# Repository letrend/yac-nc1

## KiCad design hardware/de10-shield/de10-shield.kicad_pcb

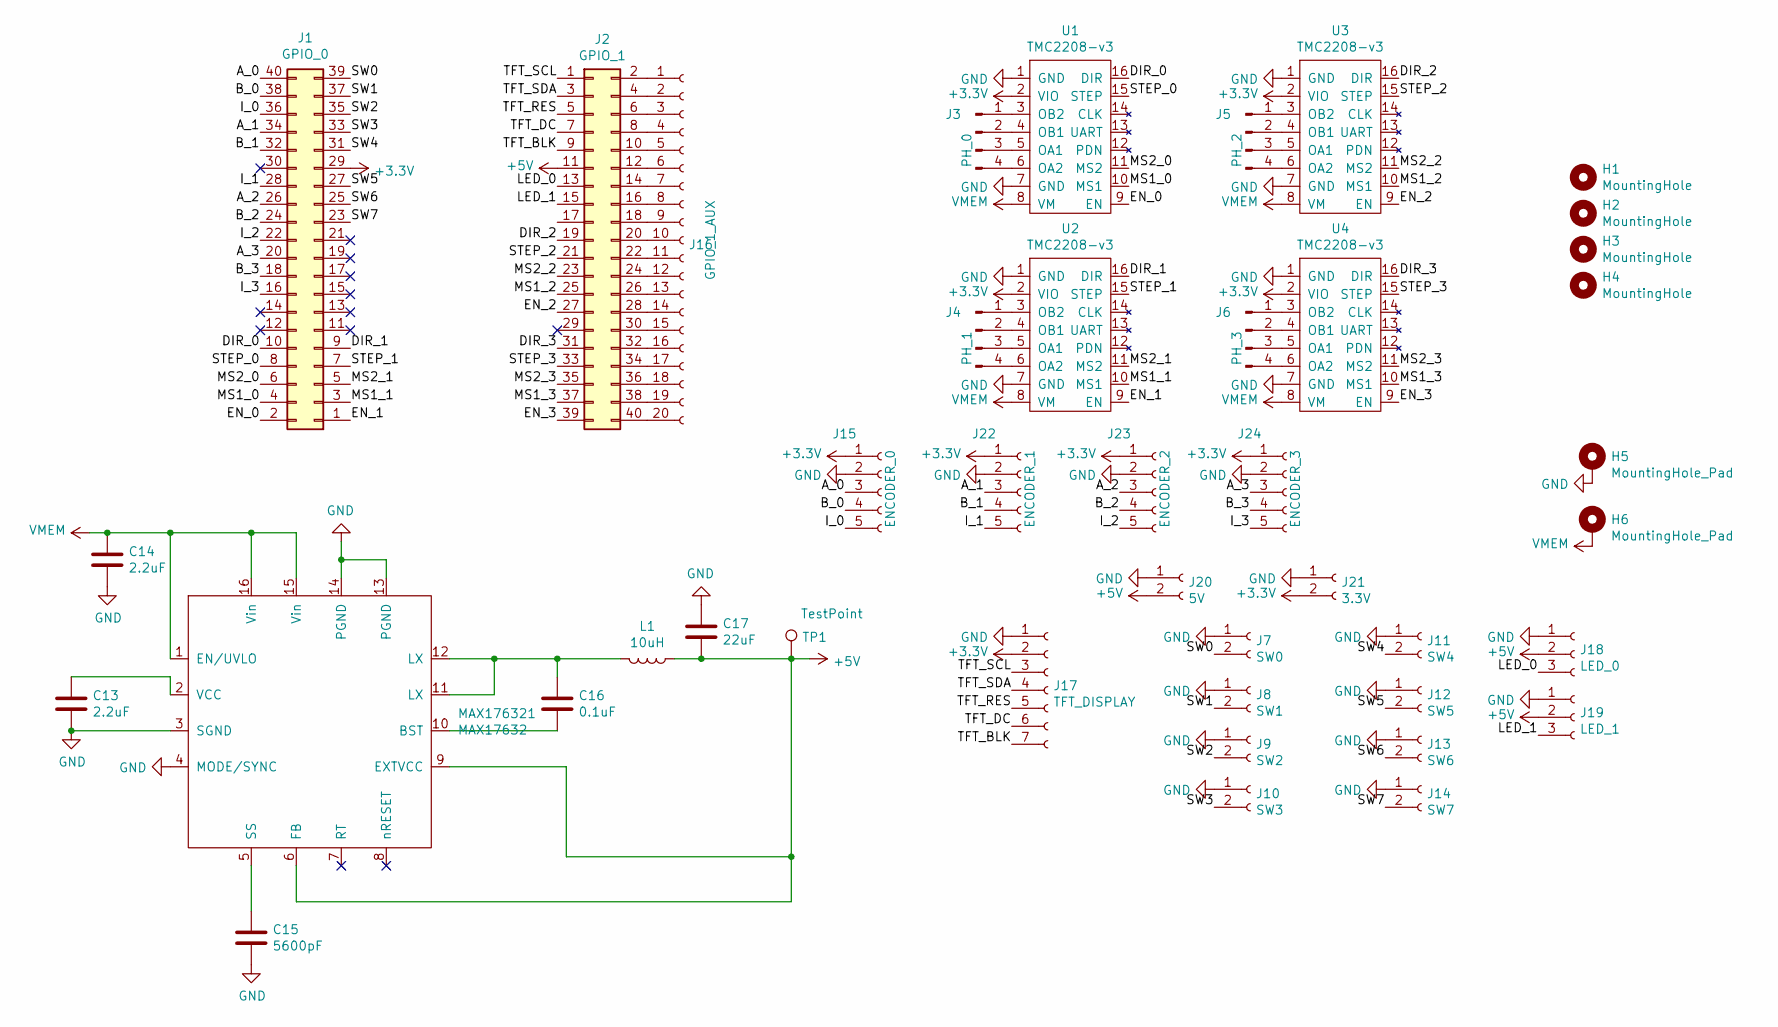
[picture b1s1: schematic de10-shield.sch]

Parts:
C13, C14: 2.2uF; C_0603_1608Metric
C15: 5600pF; C_0402_1005Metric
C16: 0.1uF; C_0402_1005Metric
C17: 22uF; C_0805_2012Metric
H1, H2, H3, H4: MountingHole; MountingHole_3.2mm_M3
H5, H6: MountingHole_Pad; MountingHole_3.2mm_M3_DIN965_Pad
J1: GPIO_0; PinSocket_2x20_P2.54mm_Vertical
J2: GPIO_1; PinSocket_2x20_P2.54mm_Vertical
J3: PH_0; PinHeader_1x04_P2.54mm_Vertical
J4: PH_1; PinHeader_1x04_P2.54mm_Vertical
J5: PH_2; PinHeader_1x04_P2.54mm_Vertical
J6: PH_3; PinHeader_1x04_P2.54mm_Vertical
J7: SW0; PinHeader_1x02_P2.54mm_Vertical
J8: SW1; PinHeader_1x02_P2.54mm_Vertical
J9: SW2; PinHeader_1x02_P2.54mm_Vertical
J10: SW3; PinHeader_1x02_P2.54mm_Vertical
J11: SW4; PinHeader_1x02_P2.54mm_Vertical
J12: SW5; PinHeader_1x02_P2.54mm_Vertical
J13: SW6; PinHeader_1x02_P2.54mm_Vertical
J14: SW7; PinHeader_1x02_P2.54mm_Vertical
J15: ENCODER_0; PinSocket_1x05_P2.54mm_Vertical
J16: GPIO_1_AUX; PinSocket_1x20_P2.54mm_Vertical
J17: TFT_DISPLAY; PinHeader_1x07_P2.54mm_Vertical
J18: LED_0; PinHeader_1x03_P2.54mm_Vertical
J19: LED_1; PinHeader_1x03_P2.54mm_Vertical
J20: 5V; PinHeader_1x02_P2.54mm_Vertical
J21: 3.3V; PinHeader_1x02_P2.54mm_Vertical
J22: ENCODER_1; PinSocket_1x05_P2.54mm_Vertical
J23: ENCODER_2; PinSocket_1x05_P2.54mm_Vertical
J24: ENCODER_3; PinSocket_1x05_P2.54mm_Vertical
L1: 10uH; XAL5050-103MEC
MAX176321: MAX17632; QFN-16-1EP_3x3mm_Pitch0.5mm
TP1: TestPoint; TestPoint_Pad_D1.0mm
U1, U2, U3, U4: TMC2208-v3; TMC2208-v3.0

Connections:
+3V3: J1.29, J15.1, J17.2, J21.2, J22.1, J23.1, J24.1, U1.2 (VIO), U2.2 (VIO), U3.2 (VIO), U4.2 (VIO)
+5V: C17.2, J2.11, J18.2, J19.2, J20.2, L1.1, MAX176321.6 (FB), MAX176321.9 (EXTVCC), TP1.1
/A_0: J1.40, J15.3
/A_1: J1.34, J22.3
/A_2: J1.26, J23.3
/A_3: J1.20, J24.3
/B_0: J1.38, J15.4
/B_1: J1.32, J22.4
/B_2: J1.24, J23.4
/B_3: J1.18, J24.4
/DIR_0: J1.10, U1.16 (DIR)
/DIR_1: J1.9, U2.16 (DIR)
/DIR_2: J2.19, U3.16 (DIR)
/DIR_3: J2.31, U4.16 (DIR)
/EN_0: J1.2, U1.9 (EN)
/EN_1: J1.1, U2.9 (EN)
/EN_2: J2.27, U3.9 (EN)
/EN_3: J2.39, U4.9 (EN)
/I_0: J1.36, J15.5
/I_1: J1.28, J22.5
/I_2: J1.22, J23.5
/I_3: J1.16, J24.5
/LED_0: J2.13, J18.3
/LED_1: J2.15, J19.3
/MS1_0: J1.4, U1.10 (MS1)
/MS1_1: J1.3, U2.10 (MS1)
/MS1_2: J2.25, U3.10 (MS1)
/MS1_3: J2.37, U4.10 (MS1)
/MS2_0: J1.6, U1.11 (MS2)
/MS2_1: J1.5, U2.11 (MS2)
/MS2_2: J2.23, U3.11 (MS2)
/MS2_3: J2.35, U4.11 (MS2)
/STEP_0: J1.8, U1.15 (STEP)
/STEP_1: J1.7, U2.15 (STEP)
/STEP_2: J2.21, U3.15 (STEP)
/STEP_3: J2.33, U4.15 (STEP)
/SW0: J1.39, J7.2
/SW1: J1.37, J8.2
/SW2: J1.35, J9.2
/SW3: J1.33, J10.2
/SW4: J1.31, J11.2
/SW5: J1.27, J12.2
/SW6: J1.25, J13.2
/SW7: J1.23, J14.2
/TFT_BLK: J2.9, J17.7
/TFT_DC: J2.7, J17.6
/TFT_RES: J2.5, J17.5
/TFT_SCL: J2.1, J17.3
/TFT_SDA: J2.3, J17.4
GND: C13.2, C14.2, C15.2, C17.1, H5.1, J7.1, J8.1, J9.1, J10.1, J11.1, J12.1, J13.1, J14.1, J15.2, J17.1, J18.1, J19.1, J20.1, J21.1, J22.2, J23.2, J24.2, MAX176321.3 (SGND), MAX176321.4 (MODE/SYNC), MAX176321.13 (PGND), MAX176321.14 (PGND), U1.1 (GND), U1.7 (GND), U2.1 (GND), U2.7 (GND), U3.1 (GND), U3.7 (GND), U4.1 (GND), U4.7 (GND); also elsewhere on the board
unnamed: C13.1, MAX176321.2 (VCC)
unnamed: C15.1, MAX176321.5 (SS)
unnamed: C16.1, L1.2, MAX176321.11 (LX), MAX176321.12 (LX)
unnamed: C16.2, MAX176321.10 (BST)
unnamed: J3.1, U1.3 (OB2)
unnamed: J3.2, U1.4 (OB1)
unnamed: J3.3, U1.5 (OA1)
unnamed: J3.4, U1.6 (OA2)
unnamed: J4.1, U2.3 (OB2)
unnamed: J4.2, U2.4 (OB1)
unnamed: J4.3, U2.5 (OA1)
unnamed: J4.4, U2.6 (OA2)
unnamed: J5.1, U3.3 (OB2)
unnamed: J5.2, U3.4 (OB1)
unnamed: J5.3, U3.5 (OA1)
unnamed: J5.4, U3.6 (OA2)
unnamed: J6.1, U4.3 (OB2)
unnamed: J6.2, U4.4 (OB1)
unnamed: J6.3, U4.5 (OA1)
unnamed: J6.4, U4.6 (OA2)
unnamed: J2.2, J16.1
unnamed: J2.4, J16.2
unnamed: J2.6, J16.3
unnamed: J2.8, J16.4
unnamed: J2.10, J16.5
unnamed: J2.12, J16.6
unnamed: J2.14, J16.7
unnamed: J2.16, J16.8
unnamed: J2.18, J16.9
unnamed: J2.20, J16.10
unnamed: J2.22, J16.11
unnamed: J2.24, J16.12
unnamed: J2.26, J16.13
unnamed: J2.28, J16.14
unnamed: J2.30, J16.15
unnamed: J2.32, J16.16
unnamed: J2.34, J16.17
unnamed: J2.36, J16.18
unnamed: J2.38, J16.19
unnamed: J2.40, J16.20
VMEM: C14.1, H6.1, MAX176321.1 (EN/UVLO), MAX176321.15 (Vin), MAX176321.16 (Vin), U1.8 (VM), U2.8 (VM), U3.8 (VM), U4.8 (VM)

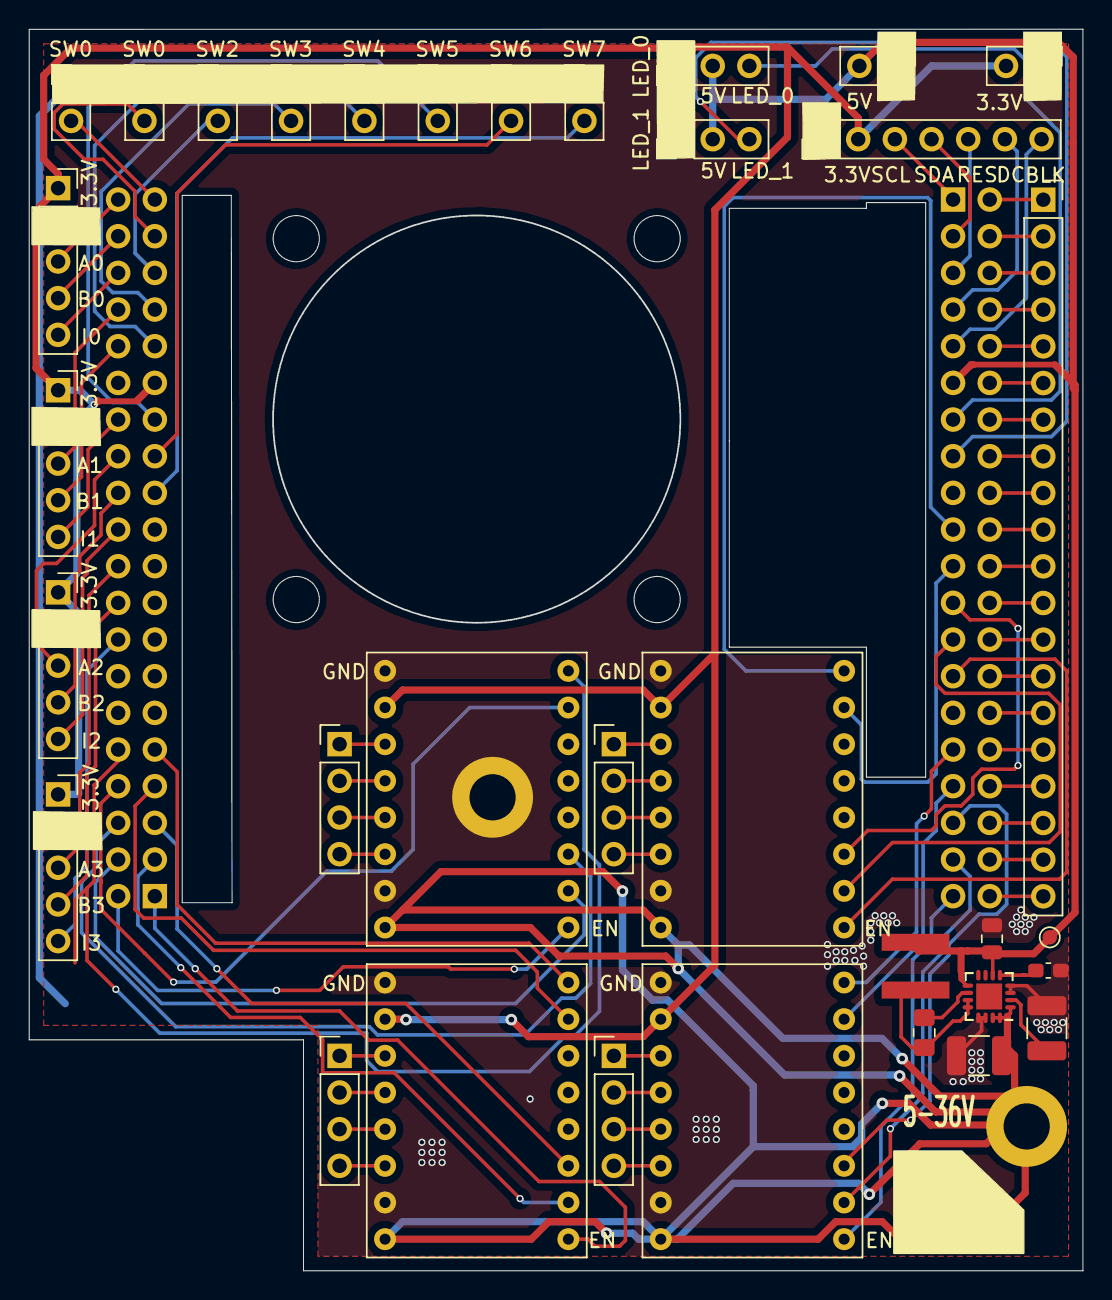
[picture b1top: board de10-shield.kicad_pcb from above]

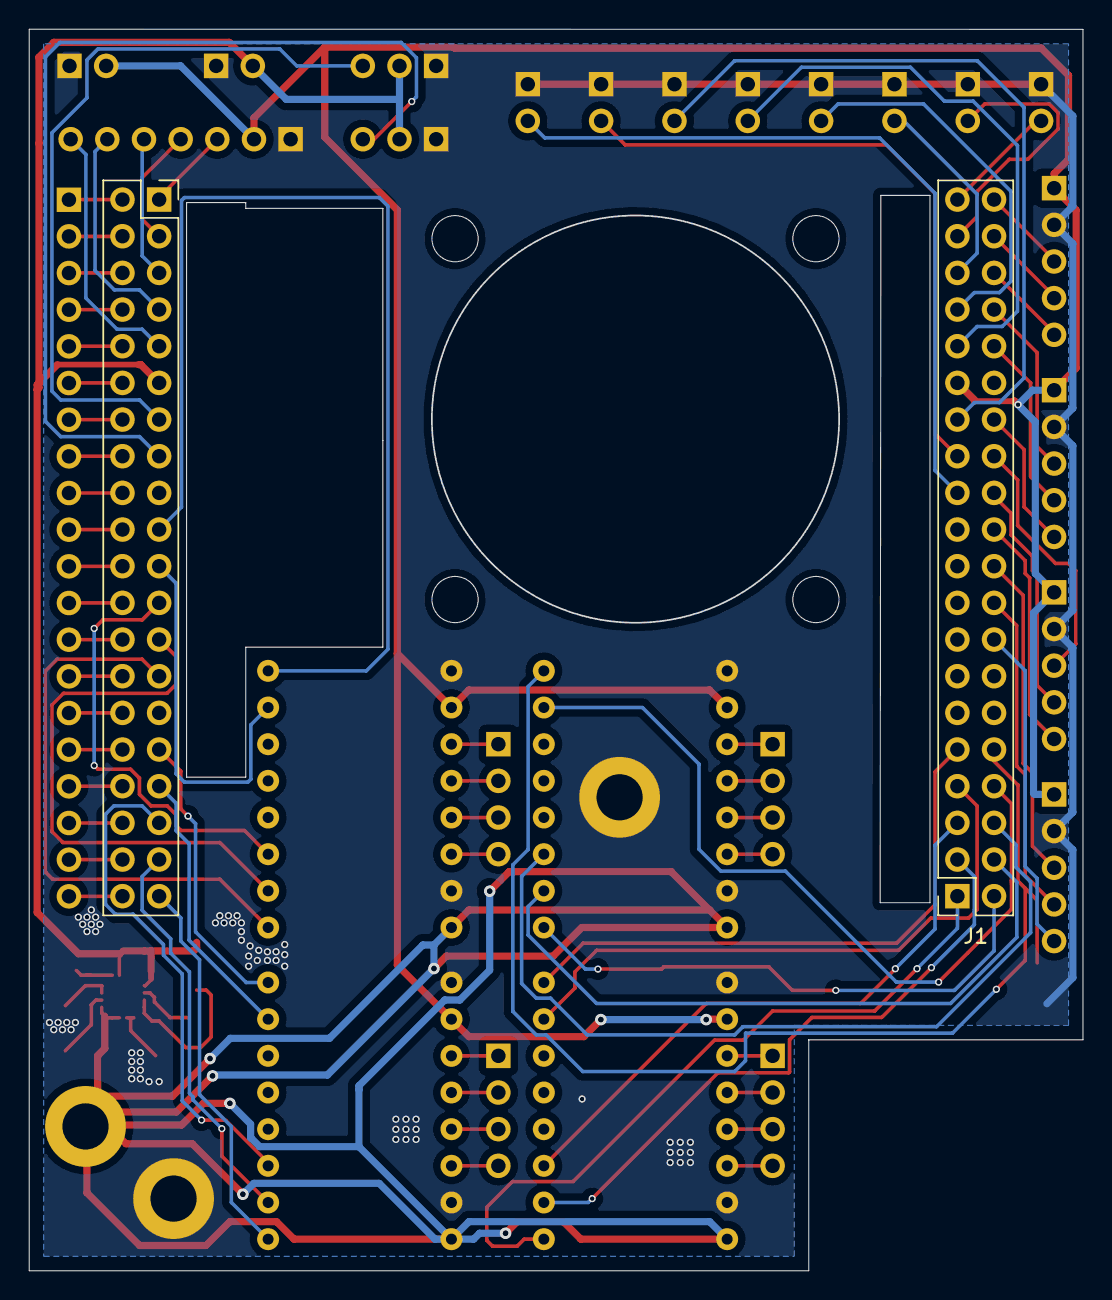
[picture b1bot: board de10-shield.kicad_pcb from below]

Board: 2 copper layers, 72.9 x 85.9 mm, 43 parts (2 on the bottom side), 91 nets.

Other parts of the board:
H7: MountingHole_Pad; MountingHole_3.2mm_M3_DIN965_Pad

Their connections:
GND: H7.1; also elsewhere on the board

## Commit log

2021-03-18 started layout
2021-03-18 done
2021-03-18 done and ordered
2021-03-23 with de10 shield pinout
2021-03-23 with gui and fpga code
2021-03-26 for de10
2021-03-26 ok ok
2021-03-27 with double speed
2021-03-29 fixed endswicth address
2021-03-29 faster
2021-03-29 zero then 1 millimeter back off
2021-04-02 with cleanser control
2021-04-30 fixed some bugs
2021-04-30 fixed some stuff
2021-05-01 with cleanser functionality and visual checkConfirm
2021-05-01 with pause stop draft
2021-05-01 bug free??
2021-05-01 docs draft
2021-05-01 try this?
2021-05-02 path
2021-05-02 cubeshot
2021-05-02 with safer save move function
2021-05-02 without led text
2021-05-02 with wANRING SIGNS
2021-05-03 bug free????
2021-05-03 with tool offset
2021-05-04 almost bug free
2021-05-04 bugs free
2024-02-16 different v4l2-ctl commands
2024-03-05 qt thread safe
2024-03-05 96 cubes per well
2024-03-07 thread safe ui
2024-03-07 with light enable signals
2024-03-07 fixed timeout
2024-03-07 grabbing frames again, after failed qr code detection
